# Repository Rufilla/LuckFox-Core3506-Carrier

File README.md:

<!-- {{LOGO — add the Rufilla logo here once an asset lives in this repo, e.g. }} -->

# Foxbridge — Luckfox Core3506 carrier board

<!-- Add build and release badges when CI is set up. -->

A carrier board for the [Luckfox Core3506](https://wiki.luckfox.com/Core3506/Introduction/)
system-on-module (SoM), for anyone who wants the RK3506 on a Raspberry Pi Model B-sized board
(85 × 56 mm) with Ethernet, USB-C, a DSI display & a 40-pin header. Designed in KiCad 10 by
Rufilla Ltd., from the [Luckfox Lyra Pi](https://www.luckfox.com/Luckfox-Lyra-Pi) reference
design. Revision A is a prototype: it has been built & brought up, with three hardware faults.

| | |
|---|---|
| **Client** | Internal |
| **Project code** | Foxbridge |
| **Status** | Prototype — Revision A built & reworked; Revision B in design |

> **Revision A has been built & brought up with three hardware faults.** USB host (OTG1) does
> not work without two reworks. Read the [errata](docs/errata.md) before ordering boards.

## Overview

The board breaks the Core3506 SoM out to a Raspberry Pi Model B footprint. Each subsystem has
its own schematic sheet; [docs/design-notes.md](docs/design-notes.md) explains how each one
works & why.

- **USB-C ×2** — OTG0 (device, flashing & 5 V power input) & OTG1 (host, 500 mA current limit)
- **10/100 Ethernet** — CH182H2 PHY on RMII0, HR911105A RJ45 with integrated magnetics
- **MIPI DSI** — 2-lane, 22-pin 0.5 mm FPC for the Luckfox 7" DSI touchscreen (SKU 25265)
- **40-pin header** — Raspberry Pi-compatible pinout
- **microSD** — TF-110 socket with power switching; see errata E4 for the eMMC SoM
- **RESET & RECOVERY buttons**; UART0 header & Qwiic connector (both not fitted)
- **4-layer, 1.6 mm, impedance-controlled** — built for JLCPCB Economic PCBA

Out of scope for this design:

- No on-board 3.3 V regulator is fitted; the SoM supplies `VCC_3V3`. U2 is reserved for a
  future Wi-Fi/Bluetooth module.
- No Wi-Fi or Bluetooth.
- Power comes only from 5 V on the OTG0 USB-C port — no barrel jack & no PoE.
- The microSD slot does not work with the Core3506 variant that has on-module eMMC.
- No MASKROM button & no mounting holes in Revision A.

## Requirements

**Hardware**

- Luckfox Core3506 SoM (RK3506), fitted to a Foxbridge carrier board, revision A
- USB-C cable on OTG0 for power & flashing; 3.3 V USB-UART on the UART0 header for a console
- Optional: Luckfox 7" DSI touchscreen (SKU 25265), microSD card, Ethernet cable

**Software**

- KiCad 10.0 or later. Checked with 10.0.6.
- [Fabrication Toolkit](https://github.com/bennymeg/JLC-Plugin-for-KiCad) plugin, to regenerate
  the JLCPCB production files
- Third-party symbol & footprint libraries, needed only to update a part from its library:

| Nickname in the design | Library | Install from |
|---|---|---|
| `PCM_SparkFun-*` | SparkFun KiCad Libraries | Plugin & Content Manager (PCM) |
| `PCM_*_AKL` | [Alternate KiCad Library](https://github.com/DawidCislo/Alternate-KiCad-Library) | PCM |
| `PCM_JLCPCB*` | [JLCPCB KiCad Library](https://github.com/CDFER/JLCPCB-Kicad-Library) | PCM, after adding CD_FER's repository |
| `digikey-footprints`, `dk_*` | [Digi-Key KiCad Library](https://github.com/Digi-Key/digikey-kicad-library) | Clone & register by hand (J3 only) |

PCM libraries resolve only with the default nickname prefix `PCM_` (**Preferences → Packages
& Updates**).

## Getting the source

```bash
git clone https://github.com/Rufilla/LuckFox-Core3506-Carrier.git
cd LuckFox-Core3506-Carrier
```

## Building

Open `luckfox_core3506_adapter.kicad_pro` in KiCad. The schematic & board carry a copy of every
symbol & footprint, so the design opens, plots & runs ERC/DRC without the third-party libraries
above. Parts specific to this board are in the project library `lib/` (nickname `Foxbridge`),
with their 3D models embedded.

Regenerate the fabrication outputs from the PCB editor with **Tools → External Plugins →
Fabrication Toolkit**. It reads `fabrication-toolkit-options.json`, excludes do-not-populate
parts & writes the Gerbers, drill, BOM & placement files that are committed in `production/`.

## Flashing / deployment

Ordering Revision A from JLCPCB, in full, is in
[docs/manufacturing.md](docs/manufacturing.md#order-from-jlcpcb). In short:

| File | Upload as |
|---|---|
| `production/luckfox_core3506_adapter.zip` | Gerbers & drill |
| `production/bom.csv` | Bill of materials |
| `production/positions.csv` | Component placement (CPL) |

Order Economic PCBA. Three parts are soldered by hand — J1 (RJ45), H1 (2 × 20 pin header) &
U1 (Core3506) — and the placement preview needs the rotation & offset corrections listed in the
manufacturing notes.

> **NOTE:** the files in `production/` reproduce Revision A exactly, including the faults in
> [docs/errata.md](docs/errata.md). Boards built from them need the E1 & E2 reworks before USB
> host works.

## Usage

Power the board from 5 V over the OTG0 USB-C port; the same port flashes the SoM. The console
is on the UART0 header. Ethernet, DSI & the 40-pin header need no board-level configuration.

Before trusting a freshly built board, check it against the reworks in
[docs/errata.md](docs/errata.md): R3 moved (E1) & R6/R7 bridged (E2). Photographs of both are
in `images/`.

## Testing

Run electrical rules & design rules from the project directory:

```bash
kicad-cli sch erc luckfox_core3506_adapter.kicad_sch
kicad-cli pcb drc --schematic-parity luckfox_core3506_adapter.kicad_pcb
```

Every outstanding ERC & DRC report is listed, with its cause & whether it is a real fault, in
[docs/manufacturing.md](docs/manufacturing.md#erc--drc-status). Schematic parity & unconnected
items are both zero.

## Project structure

```
luckfox_core3506_adapter.kicad_pro   KiCad project; the root schematic, 10 sheets & board sit beside it
lib/                                 Project symbol library & footprint library
production/                          Revision A files as ordered from JLCPCB: Gerbers & drill (.zip), BOM, placement, IPC netlist
docs/                                Design notes, errata, manufacturing notes & the Revision B checklist
images/                              Board render & rework photographs
```

Documentation:

- [Design notes](docs/design-notes.md) — how each subsystem works & why
- [Errata](docs/errata.md) — Revision A faults, reworks & limitations
- [Manufacturing](docs/manufacturing.md) — stack-up, ordering from JLCPCB, ERC/DRC status
- [Revision B checklist](docs/rev-b-checklist.md) — changes planned for the respin

## Security

Report a security problem to [hello@rufilla.com](mailto:hello@rufilla.com) rather than through
a public issue. This repository holds hardware design files only, so no software bill of
materials (SBOM) is produced; the bill of materials for the board is `production/bom.csv`.

## Contributing

Report problems & suggestions through GitHub issues, & send changes as pull requests.

## Licence

Copyright 2026 Rufilla Ltd. Licensed under the [Apache License 2.0](LICENSE).

Symbols, footprints & 3D models copied from third-party libraries remain under their own
licences.

## Support

Rufilla Ltd · Building D5, Culham Campus, Abingdon, Oxfordshire, UK, OX14 3DB
[hello@rufilla.com](mailto:hello@rufilla.com) · +44 (0)1865 601201 · [www.rufilla.com](https://www.rufilla.com)

© 2026 Rufilla Ltd

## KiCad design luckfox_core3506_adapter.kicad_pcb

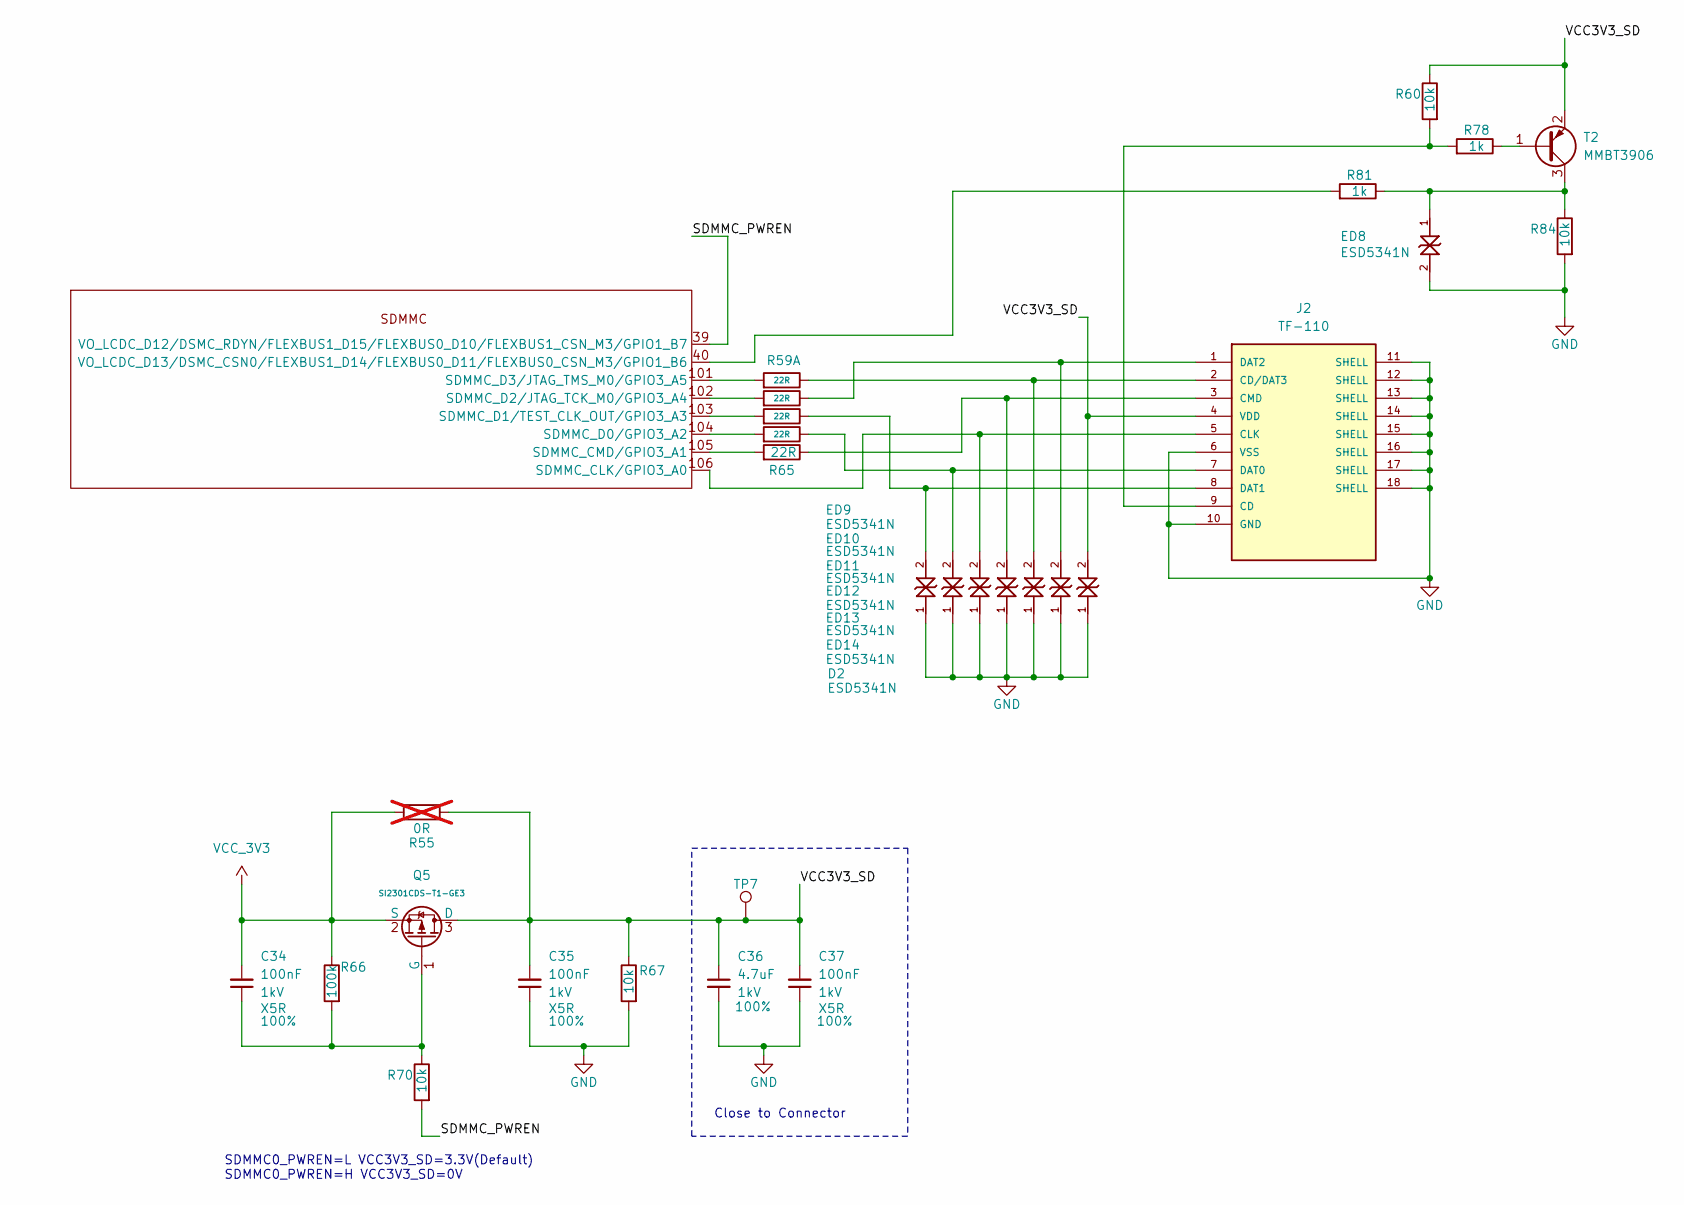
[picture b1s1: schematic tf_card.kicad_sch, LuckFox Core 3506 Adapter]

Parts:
C34, C35, C37: 100nF; C_0603_1608Metric; Voltage 1kV; Tolerance 100%; LCSC C14663
C36: 4.7uF; C_0603_1608Metric; Voltage 1kV; Tolerance 100%; LCSC C19666
D2: ESD5341N; D_0402_1005Metric; LCSC C20612964
ED8, ED9, ED10, ED11, ED12, ED13, ED14: ESD5341N; D_0402_1005Metric; LCSC C20612964
J2: TF-110; TF-SMD_TF-110; LCSC C266613
Q5: SI2301CDS-T1-GE3; Q_SOT-23; Part SI2301CDS-T1-GE3; LCSC C10487
R55: 0R; R_0603_1608Metric; LCSC C21189; not fitted
R59: 22R; R_0603x4; Tolerance ±5%; Part 4D03WGJ0220T5E; LCSC C12008
R60, R67, R70, R84: 10k; R_0603_1608Metric; LCSC C25804
R65: 22R; R_0603_1608Metric; LCSC C23345
R66: 100k; R_0603_1608Metric; LCSC C25803
R78, R81: 1k; R_0603_1608Metric; LCSC C21190
T2: MMBT3906; SOT23-3; LCSC C2149
TP7: 3.3v SD; TestPoint-1.0mm
U1: CORE3506_[32_32]_120P

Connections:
/TF card/SDMMC_PWREN: R70.1, U1.39 (VO_LCDC_D12/DSMC_RDYN/FLEXBUS1_D15/FLEX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)
/TF card/VCC3V3_SD: C35.2, C36.1, C37.2, D2.2 (A2), J2.4 (VDD), Q5.3 (D), R55.1, R60.2, R67.2, T2.2 (E), TP7.1 (1_1)
GND: C35.1, C36.2, C37.1, D2.1 (A1), ED8.2 (A2), ED9.1 (A1), ED10.1 (A1), ED11.1 (A1), ED12.1 (A1), ED13.1 (A1), ED14.1 (A1), J2.6 (VSS), J2.10 (GND), J2.11 (SHELL), J2.12 (SHELL), J2.13 (SHELL), J2.14 (SHELL), J2.15 (SHELL), J2.16 (SHELL), J2.17 (SHELL), J2.18 (SHELL), R67.1, R84.1; also elsewhere on the board
unnamed: ED8.1 (A1), R81.2, R84.2, T2.3 (C)
unnamed: ED9.2 (A2), J2.8 (DAT1), R59.7
unnamed: ED10.2 (A2), J2.7 (DAT0), R59.8
unnamed: ED11.2 (A2), J2.5 (CLK), U1.106 (SDMMC_CLK/GPIO3_A0)
unnamed: ED12.2 (A2), J2.3 (CMD), R65.2
unnamed: ED13.2 (A2), J2.2 (CD/DAT3), R59.5
unnamed: ED14.2 (A2), J2.1 (DAT2), R59.6
unnamed: J2.9 (CD), R60.1, R78.1
unnamed: C34.1, Q5.1 (G), R66.1, R70.2
unnamed: R78.2, T2.1 (B)
unnamed: R65.1, U1.105 (SDMMC_CMD/GPIO3_A1)
unnamed: R59.1, U1.104 (SDMMC_D0/GPIO3_A2)
unnamed: R59.2, U1.103 (SDMMC_D1/TEST_CLK_OUT/GPIO3_A3)
unnamed: R59.3, U1.102 (SDMMC_D2/JTAG_TCK_M0/GPIO3_A4)
unnamed: R59.4, U1.101 (SDMMC_D3/JTAG_TMS_M0/GPIO3_A5)
unnamed: R81.1, U1.40 (VO_LCDC_D13/DSMC_CSN0/FLEXBUS1_D14/FLEX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)
VCC_3V3: C34.2, Q5.2 (S), R55.2, R66.2; also elsewhere on the board

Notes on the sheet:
Close to Connector
SDMMC0_PWREN=L VCC3V3_SD=3.3V(Default) SDMMC0_PWREN=H VCC3V3_SD=0V

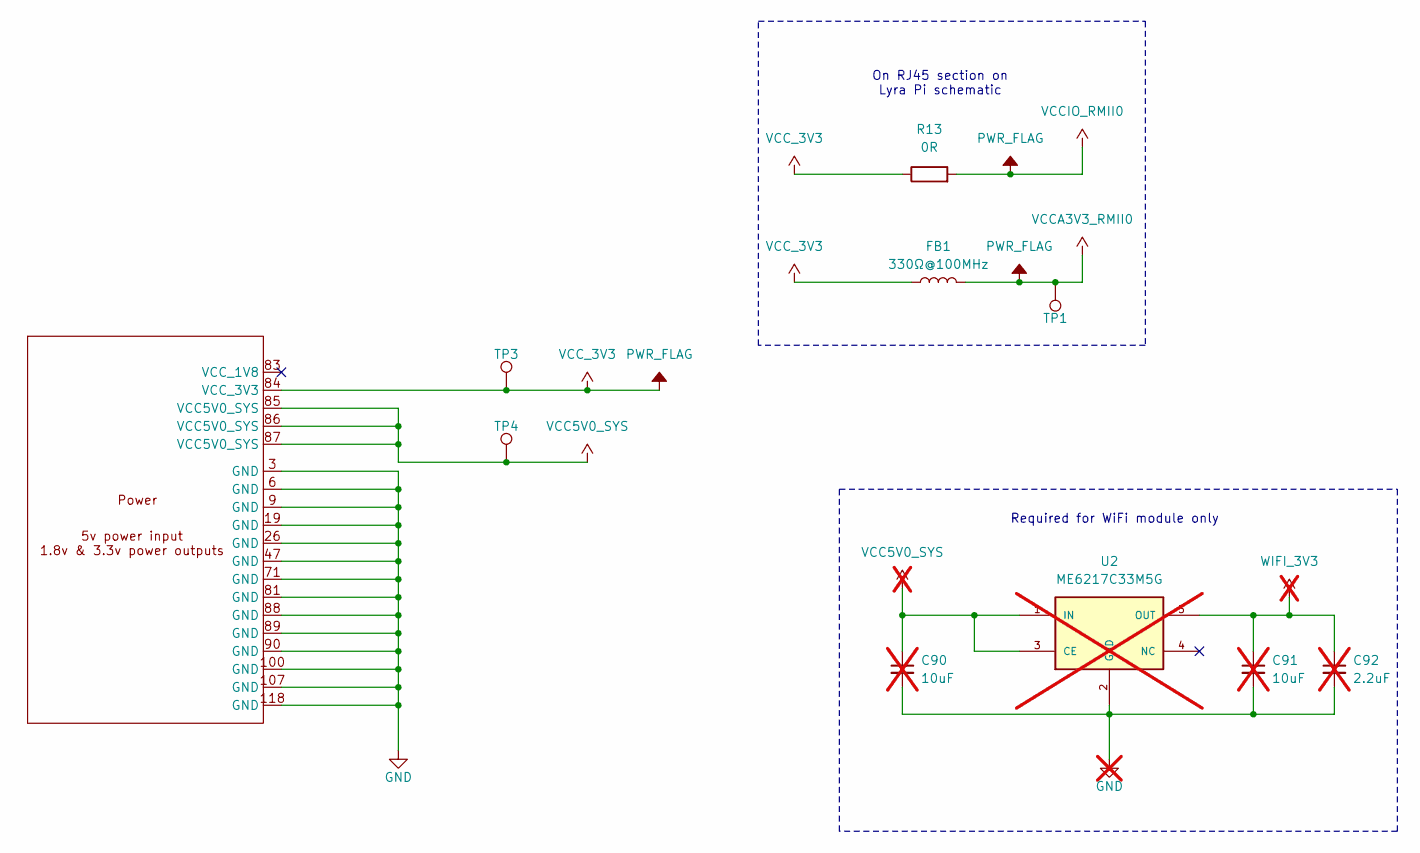
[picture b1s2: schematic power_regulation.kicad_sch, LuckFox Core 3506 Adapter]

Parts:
C90, C91: 10uF; C_0603_1608Metric; LCSC C19702; not fitted
C92: 2.2uF; C_0603_1608Metric; LCSC C23630; not fitted
FB1: 330Ω@100MHz; L_0603_1608Metric; LCSC C88989
R13: 0R; R_0603_1608Metric; LCSC C21189
TP1: 3.3v RMIIO; TestPoint-1.0mm
TP3: 3.3v; TestPoint-1.0mm
TP4: 5v; TestPoint-1.0mm
U1: CORE3506_[32_32]_120P
U2: ME6217C33M5G; SOT23-5; M_PART_NUMBER ME6217C33M5G; LCSC C427602; not fitted

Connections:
GND: C90.2, C91.2, C92.2, U1.3 (GND), U1.6 (GND), U1.9 (GND), U1.19 (GND), U1.26 (GND), U1.47 (GND), U1.71 (GND), U1.81 (GND), U1.88 (GND), U1.89 (GND), U1.90 (GND), U1.100 (GND), U1.107 (GND), U1.118 (GND), U2.2 (GND); also elsewhere on the board
VCC5V0_SYS: C90.1, TP4.1 (1_1), U1.85 (VCC5V0_SYS), U1.86 (VCC5V0_SYS), U1.87 (VCC5V0_SYS), U2.1 (IN), U2.3 (CE); also elsewhere on the board
VCCA3V3_RMII0: FB1.2, TP1.1 (1_1); also elsewhere on the board
VCCIO_RMII0: R13.2; also elsewhere on the board
VCC_3V3: FB1.1, R13.1, TP3.1 (1_1), U1.84 (VCC_3V3); also elsewhere on the board
WIFI_3V3: C91.1, C92.1, U2.5 (OUT)

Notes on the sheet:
On RJ45 section on Lyra Pi schematic
Required for WiFi module only

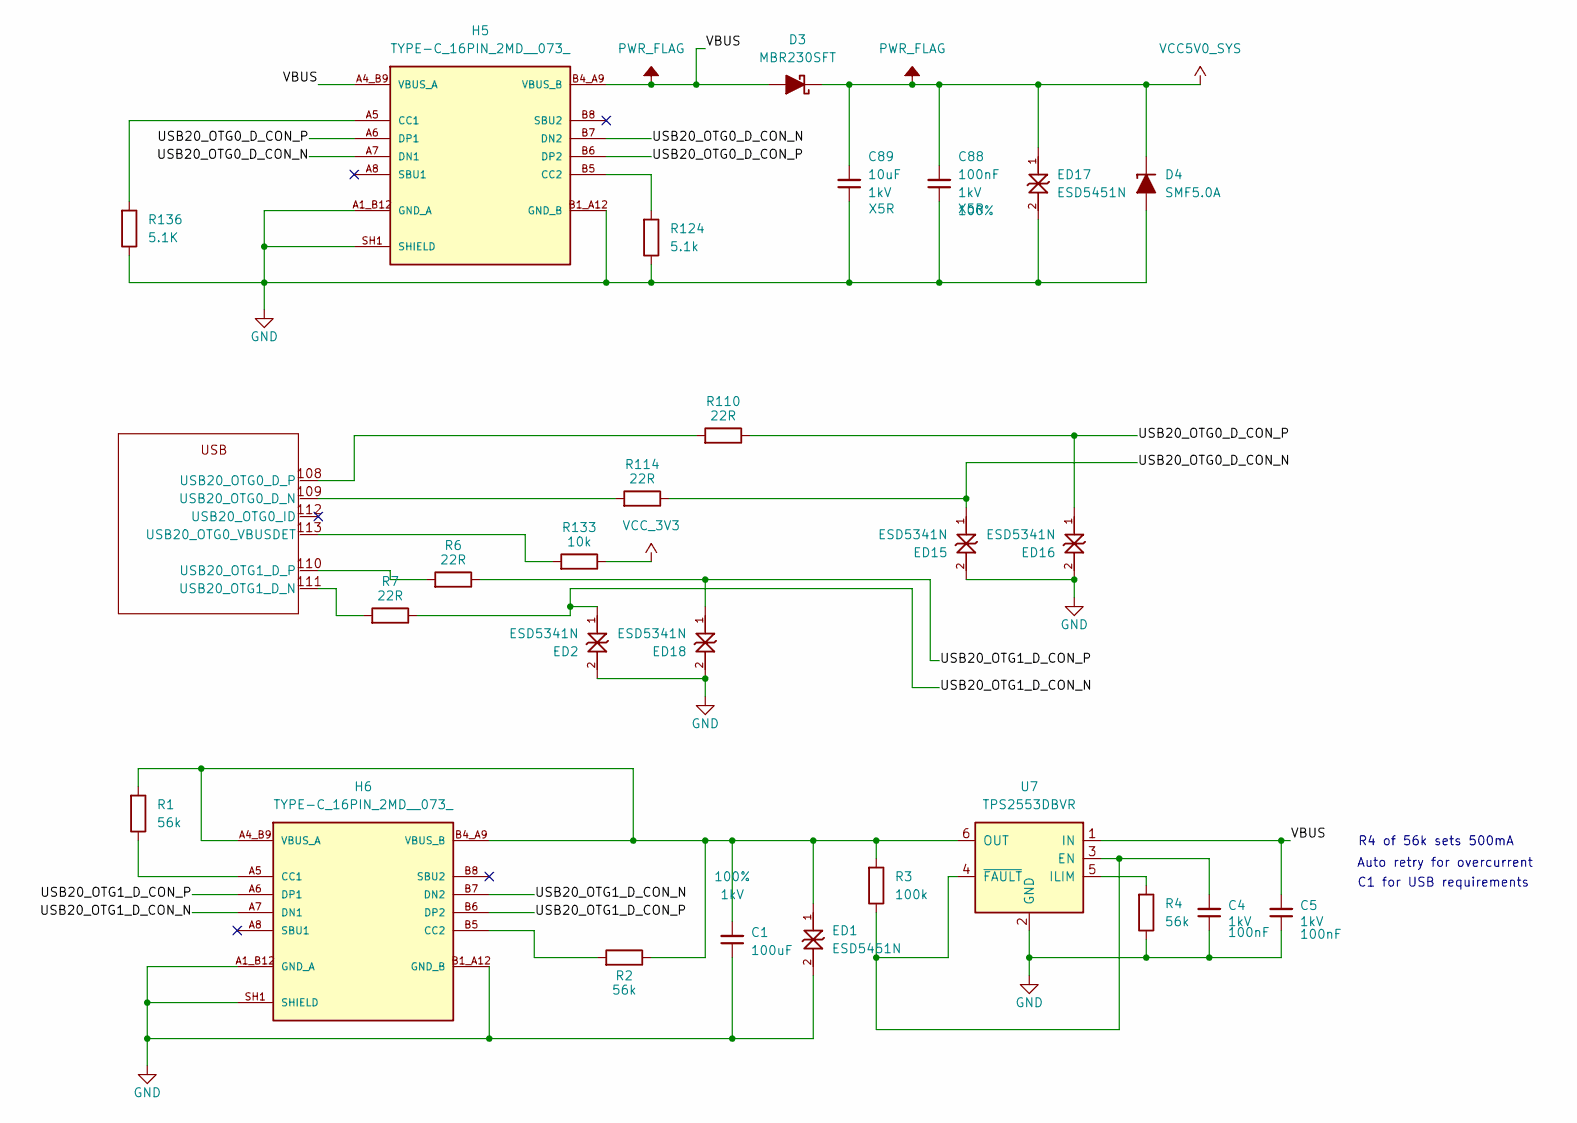
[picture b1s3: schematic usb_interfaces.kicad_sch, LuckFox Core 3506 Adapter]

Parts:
C1: 100uF; C_1206_3216Metric; Voltage 1kV; Tolerance 100%; LCSC C15008
C4, C5, C88: 100nF; C_0603_1608Metric; Voltage 1kV; Tolerance 100%; LCSC C14663
C89: 10uF; C_0603_1608Metric; Voltage 1kV; Tolerance 100%; LCSC C19702
D3: MBR230SFT; D_SOD-123F; LCSC C5377812
D4: SMF5.0A; D_SOD-123F; LCSC C19077498
ED1, ED17: ESD5451N; D_0402_1005Metric; LCSC C2936977
ED2, ED15, ED16, ED18: ESD5341N; D_0402_1005Metric; LCSC C20612964
H5, H6: TYPE-C_16PIN_2MD__073_; TYPE-C_16PIN_2MD_073; LCSC C2765186
R1, R2, R4: 56k; R_0603_1608Metric; LCSC C23206
R3: 100k; R_0603_1608Metric; LCSC C25803
R6, R7, R110, R114: 22R; R_0603_1608Metric; LCSC C23345
R124: 5.1k; R_0603_1608Metric; LCSC C23186
R133: 10k; R_0603_1608Metric; LCSC C25804
R136: 5.1K; R_0603_1608Metric; LCSC C23186
U1: CORE3506_[32_32]_120P
U7: TPS2553DBVR; SOT-23-6; LCSC C55266

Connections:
/USB interfaces/USB20_OTG0_D_CON_N: ED15.1 (A1), H5.A7 (DN1), H5.B7 (DN2), R114.2
/USB interfaces/USB20_OTG0_D_CON_P: ED16.1 (A1), H5.A6 (DP1), H5.B6 (DP2), R110.2
/USB interfaces/USB20_OTG1_D_CON_N: ED2.1 (A1), H6.A7 (DN1), H6.B7 (DN2), R7.2
/USB interfaces/USB20_OTG1_D_CON_P: ED18.1 (A1), H6.A6 (DP1), H6.B6 (DP2), R6.2
/USB interfaces/VBUS: C5.2, D3.2 (A), H5.A4_B9 (VBUS_A), H5.B4_A9 (VBUS_B), U7.1 (IN)
GND: C1.1, C4.1, C5.1, C88.1, C89.1, D4.2 (A), ED1.2 (A2), ED2.2 (A2), ED15.2 (A2), ED16.2 (A2), ED17.2 (A2), ED18.2 (A2), H5.A1_B12 (GND_A), H5.B1_A12 (GND_B), H5.SH1 (SHIELD), H5.SH2 (SHIELD), H5.SH3 (SHIELD), H5.SH4 (SHIELD), H6.A1_B12 (GND_A), H6.B1_A12 (GND_B), H6.SH1 (SHIELD), H6.SH2 (SHIELD), H6.SH3 (SHIELD), H6.SH4 (SHIELD), R4.2, R124.2, R136.2, U7.2 (GND); also elsewhere on the board
unnamed: C1.2, ED1.1 (A1), H6.A4_B9 (VBUS_A), H6.B4_A9 (VBUS_B), R1.1, R2.2, R3.1, U7.6 (OUT)
unnamed: H5.A5 (CC1), R136.1
unnamed: H5.B5 (CC2), R124.1
unnamed: H6.A5 (CC1), R1.2
unnamed: H6.B5 (CC2), R2.1
unnamed: R114.1, U1.109 (USB20_OTG0_D_N)
unnamed: R110.1, U1.108 (USB20_OTG0_D_P)
unnamed: R133.1, U1.113 (USB20_OTG0_VBUSDET)
unnamed: R7.1, U1.111 (USB20_OTG1_D_N)
unnamed: R6.1, U1.110 (USB20_OTG1_D_P)
unnamed: C4.2, R3.2, U7.3 (EN), U7.4 (~FAULT)
unnamed: R4.1, U7.5 (ILIM)
VCC5V0_SYS: C88.2, C89.2, D3.1 (K), D4.1 (K), ED17.1 (A1); also elsewhere on the board
VCC_3V3: R133.2; also elsewhere on the board

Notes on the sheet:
R4 of 56k sets 500mA
C1 for USB requirements
Auto retry for overcurrent

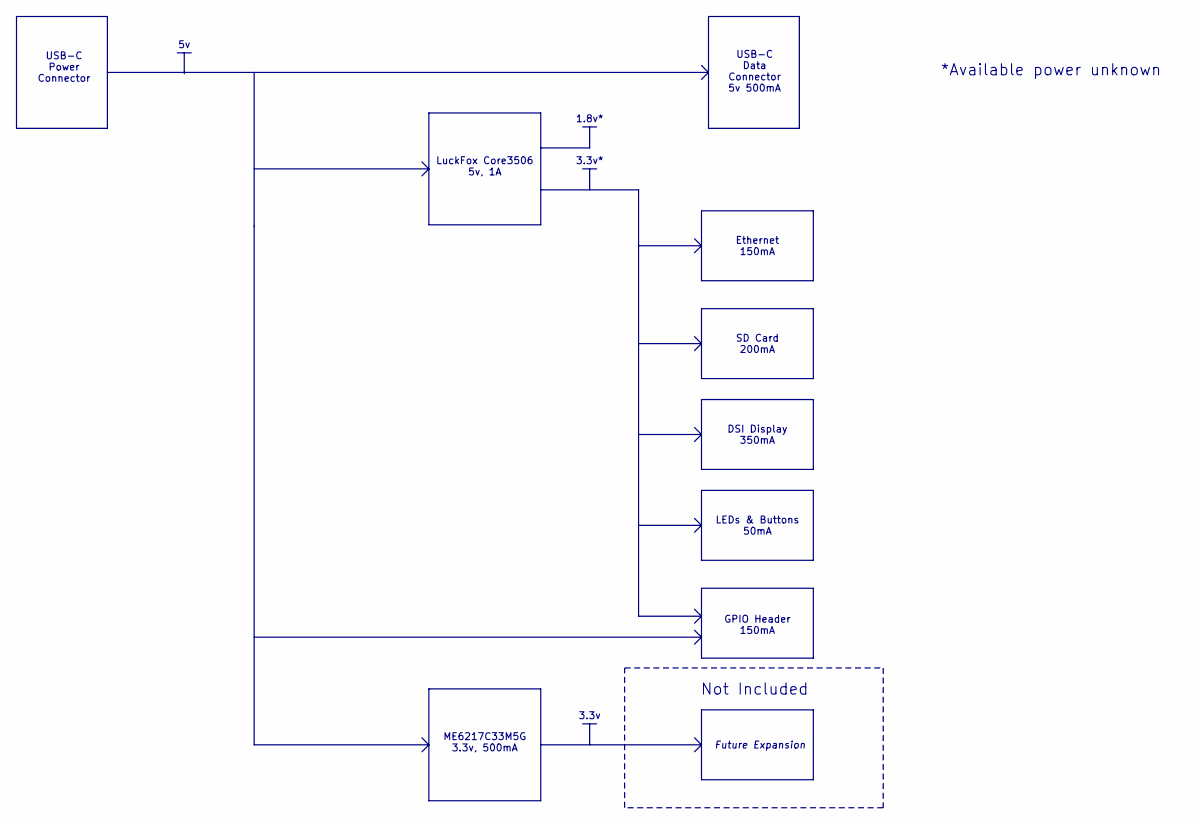
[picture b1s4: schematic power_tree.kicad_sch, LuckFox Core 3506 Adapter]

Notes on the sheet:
GPIO Header 150mA
Ethernet 150mA
*Available power unknown
DSI Display 350mA
LEDs & Buttons 50mA
USB-C Data Connector 5v 500mA
3.3v
USB-C Power Connector
1.8v*
LuckFox Core3506 5v, 1A
ME6217C33M5G 3.3v, 500mA
3.3v*
SD Card 200mA
Not Included
Future Expansion

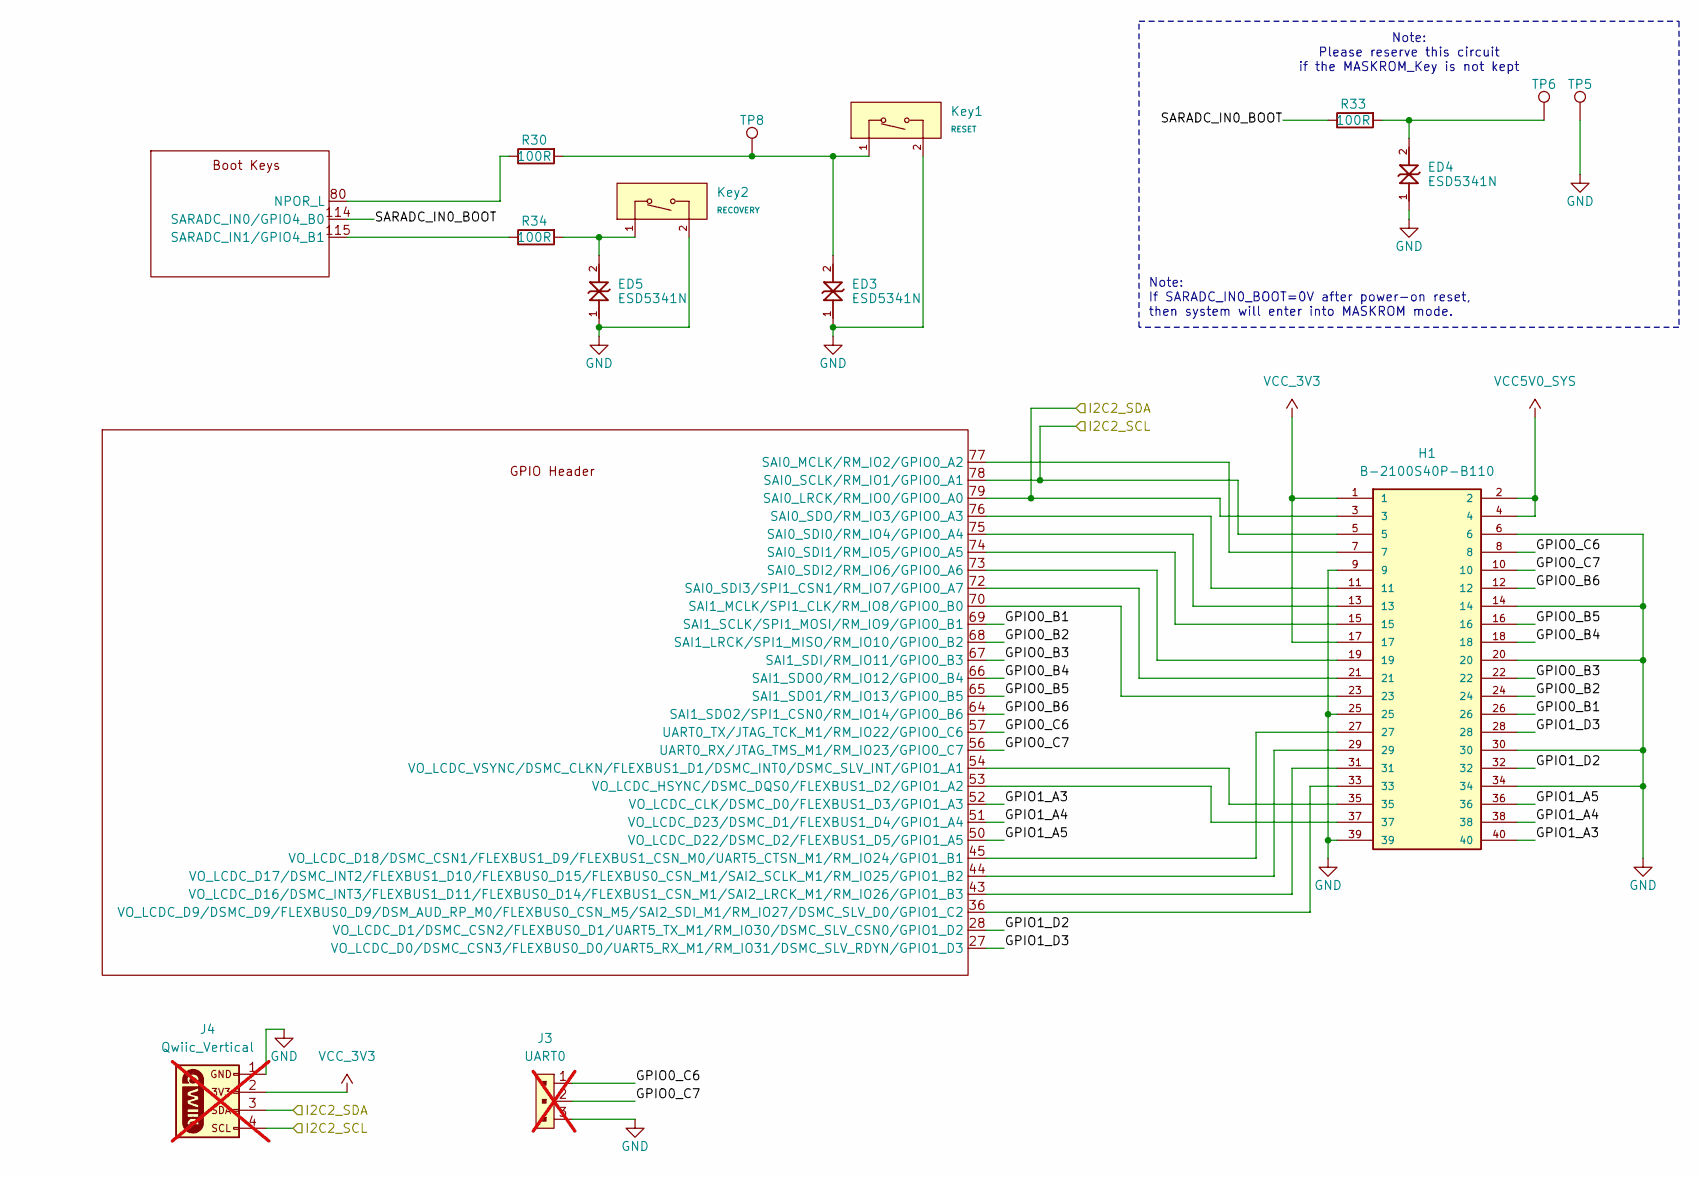
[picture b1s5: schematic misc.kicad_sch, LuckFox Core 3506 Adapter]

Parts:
ED3, ED4, ED5: ESD5341N; D_0402_1005Metric; LCSC C20612964
H1: B-2100S40P-B110; PinHeader_2x20_P2.54mm_Vertical; LCSC C124383
J3: UART0; PinHeader_1x3_P2.54_Drill1.1mm; MPN 640456-3; Digi-Key_PN A19470-ND; not fitted
J4: Qwiic_Vertical; JST_1x04_P1.0mm_Vertical_SMD; not fitted
Key1: RESET; SW_TS-1088-AR02016; Voltage Rating (Dc) 12V; Part TS-1088-AR02016; LCSC C720477
Key2: RECOVERY; SW_TS-1088-AR02016; Voltage Rating (Dc) 12V; Part TS-1088-AR02016; LCSC C720477
R30, R33, R34: 100R; R_0603_1608Metric; LCSC C22775
TP5: GND; TestPoint-1.0mm
TP6: BOOT; TestPoint-1.0mm
TP8: NPOR_L; TestPoint-1.0mm
U1: CORE3506_[32_32]_120P

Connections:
/DSI/I2C2_SCL: H1.5, J4.4, U1.78 (SAI0_SCLK/RM_IO1/GPIO0_A1); also elsewhere on the board
/DSI/I2C2_SDA: H1.3, J4.3, U1.79 (SAI0_LRCK/RM_IO0/GPIO0_A0); also elsewhere on the board
/GPIO Header & boot keys/GPIO0_B1: H1.26, U1.69 (SAI1_SCLK/SPI1_MOSI/RM_IO9/GPIO0_B1)
/GPIO Header & boot keys/GPIO0_B2: H1.24, U1.68 (SAI1_LRCK/SPI1_MISO/RM_IO10/GPIO0_B2)
/GPIO Header & boot keys/GPIO0_B3: H1.22, U1.67 (SAI1_SDI/RM_IO11/GPIO0_B3)
/GPIO Header & boot keys/GPIO0_B4: H1.18, U1.66 (SAI1_SDO0/RM_IO12/GPIO0_B4)
/GPIO Header & boot keys/GPIO0_B5: H1.16, U1.65 (SAI1_SDO1/RM_IO13/GPIO0_B5)
/GPIO Header & boot keys/GPIO0_B6: H1.12, U1.64 (SAI1_SDO2/SPI1_CSN0/RM_IO14/GPIO0_B6)
/GPIO Header & boot keys/GPIO0_C6: H1.8, J3.1, U1.57 (UART0_TX/JTAG_TCK_M1/RM_IO22/GPIO0_C6)
/GPIO Header & boot keys/GPIO0_C7: H1.10, J3.2, U1.56 (UART0_RX/JTAG_TMS_M1/RM_IO23/GPIO0_C7)
/GPIO Header & boot keys/GPIO1_A3: H1.40, U1.52 (VO_LCDC_CLK/DSMC_D0/FLEXBUS1_D3/GPIO1_A3)
/GPIO Header & boot keys/GPIO1_A4: H1.38, U1.51 (VO_LCDC_D23/DSMC_D1/FLEXBUS1_D4/GPIO1_A4)
/GPIO Header & boot keys/GPIO1_A5: H1.36, U1.50 (VO_LCDC_D22/DSMC_D2/FLEXBUS1_D5/GPIO1_A5)
/GPIO Header & boot keys/GPIO1_D2: H1.32, U1.28 (VO_LCDC_D1/DSMC_CSN2/FLEXBUS0_D1/UART5_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)
/GPIO Header & boot keys/GPIO1_D3: H1.28, U1.27 (VO_LCDC_D0/DSMC_CSN3/FLEXBUS0_D0/UART5_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)
/GPIO Header & boot keys/SARADC_IN0_BOOT: R33.2, U1.114 (SARADC_IN0/GPIO4_B0)
GND: ED3.1 (A1), ED4.1 (A1), ED5.1 (A1), H1.6, H1.9, H1.14, H1.20, H1.25, H1.30, H1.34, H1.39, J3.3, J4.1, Key1.2 (B), Key2.2 (B), TP5.1 (1_1); also elsewhere on the board
unnamed: ED3.2 (A2), Key1.1 (A), R30.1, TP8.1 (1_1)
unnamed: ED4.2 (A2), R33.1, TP6.1 (1_1)
unnamed: ED5.2 (A2), Key2.1 (A), R34.1
unnamed: R30.2, U1.80 (NPOR_L)
unnamed: R34.2, U1.115 (SARADC_IN1/GPIO4_B1)
unnamed: H1.7, U1.77 (SAI0_MCLK/RM_IO2/GPIO0_A2)
unnamed: H1.13, U1.75 (SAI0_SDI0/RM_IO4/GPIO0_A4)
unnamed: H1.15, U1.74 (SAI0_SDI1/RM_IO5/GPIO0_A5)
unnamed: H1.19, U1.73 (SAI0_SDI2/RM_IO6/GPIO0_A6)
unnamed: H1.21, U1.72 (SAI0_SDI3/SPI1_CSN1/RM_IO7/GPIO0_A7)
unnamed: H1.11, U1.76 (SAI0_SDO/RM_IO3/GPIO0_A3)
unnamed: H1.23, U1.70 (SAI1_MCLK/SPI1_CLK/RM_IO8/GPIO0_B0)
unnamed: H1.33, U1.36 (VO_LCDC_D9/DSMC_D9/FLEXBUS0_D9/DSM_AUD_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)
unnamed: H1.31, U1.43 (VO_LCDC_D16/DSMC_INT3/FLEXBUS1_D11/FLEX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)
unnamed: H1.29, U1.44 (VO_LCDC_D17/DSMC_INT2/FLEXBUS1_D10/FLEX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)
unnamed: H1.27, U1.45 (VO_LCDC_D18/DSMC_CSN1/FLEXBUS1_D9/FLEXB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)
unnamed: H1.37, U1.53 (VO_LCDC_HSYNC/DSMC_DQS0/FLEXBUS1_D2/GPI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)
unnamed: H1.35, U1.54 (VO_LCDC_VSYNC/DSMC_CLKN/FLEXBUS1_D1/DSM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)
VCC5V0_SYS: H1.2, H1.4; also elsewhere on the board
VCC_3V3: H1.1, H1.17, J4.2; also elsewhere on the board

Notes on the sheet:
Note: Please reserve this circuit if the MASKROM_Key is not kept
Note: If SARADC_IN0_BOOT=0V after power-on reset, then system will enter into MASKROM mode.

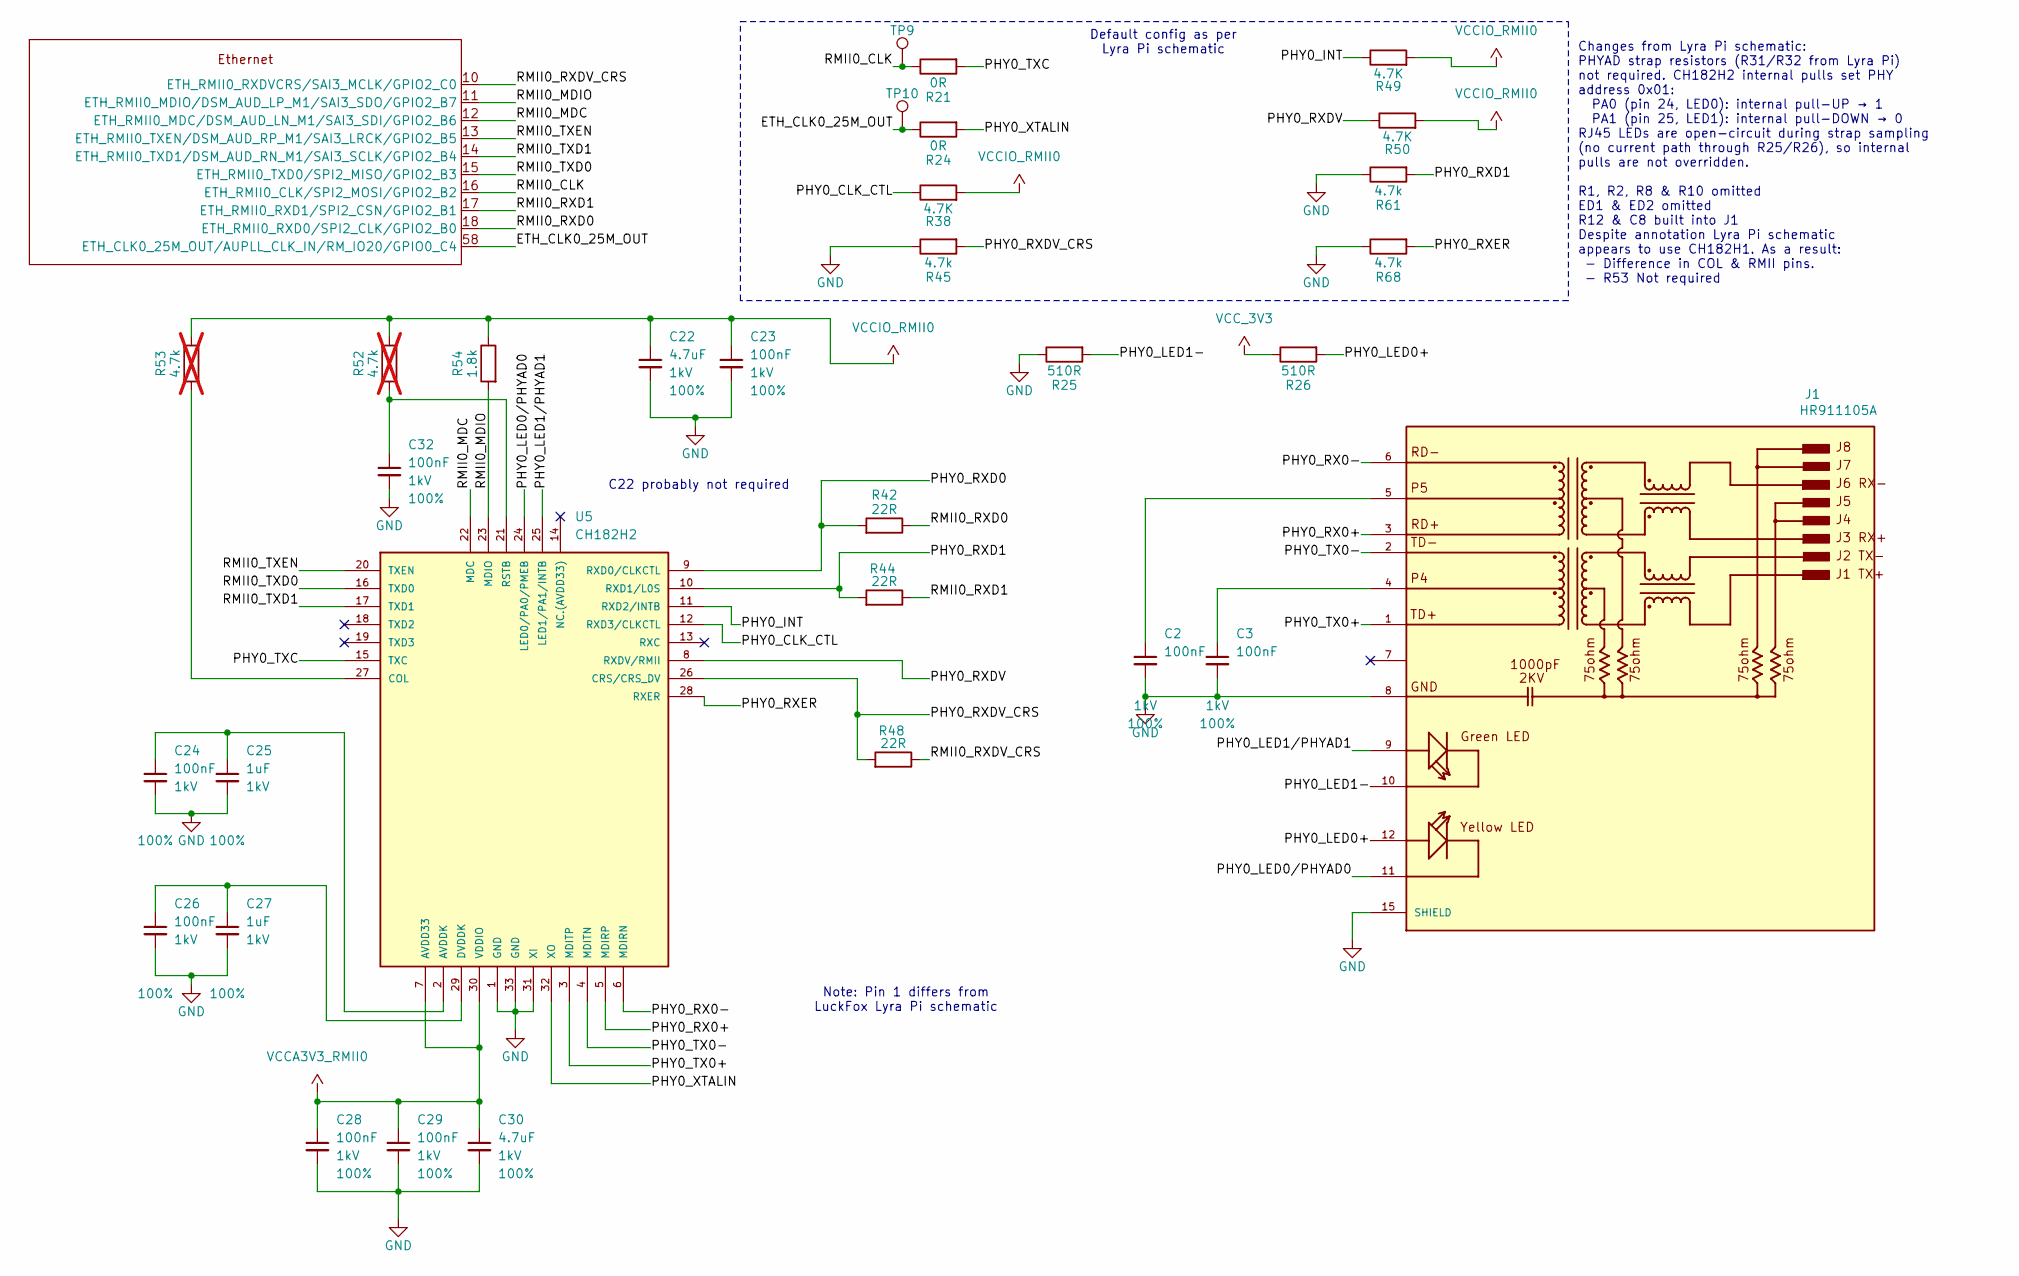
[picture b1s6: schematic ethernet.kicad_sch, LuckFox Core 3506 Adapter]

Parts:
C2, C3, C23, C24, C26, C28, C29, C32: 100nF; C_0603_1608Metric; Voltage 1kV; Tolerance 100%; LCSC C14663
C22, C30: 4.7uF; C_0603_1608Metric; Voltage 1kV; Tolerance 100%; LCSC C19666
C25, C27: 1uF; C_0603_1608Metric; Voltage 1kV; Tolerance 100%; LCSC C15849
J1: HR911105A; HANRUN_HR911105A; LCSC C12074
R21, R24: 0R; R_0603_1608Metric; LCSC C21189
R25, R26: 510R; R_0603_1608Metric; LCSC C23193
R38, R49, R50: 4.7K; R_0603_1608Metric; LCSC C23162
R42, R44, R48: 22R; R_0603_1608Metric; LCSC C23345
R45, R61, R68: 4.7k; R_0603_1608Metric; LCSC C23162
R52, R53: 4.7k; R_0603_1608Metric; LCSC C23162; not fitted
R54: 1.8k; R_0603_1608Metric; LCSC C4177
TP9: RMII0_CLK; TestPoint-1.0mm
TP10: ETH_CLK; TestPoint-1.0mm
U1: CORE3506_[32_32]_120P
U5: CH182H2; QFN-32-1EP_5x5mm_P0.5mm_EP3.45x3.45mm; LCSC C41427683

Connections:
/Ethernet/ETH_CLK0_25M_OUT: R24.2, TP10.1 (1_1), U1.58 (ETH_CLK0_25M_OUT/AUPLL_CLK_IN/RM_IO20/G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)
/Ethernet/PHY0_CLK_CTL: R38.1, U5.12 (RXD3/CLKCTL)
/Ethernet/PHY0_INT: R49.1, U5.11 (RXD2/INTB)
/Ethernet/PHY0_LED0+: J1.12, R26.1
/Ethernet/PHY0_LED0/PHYAD0: J1.11, U5.24 (LED0/PA0/PMEB)
/Ethernet/PHY0_LED1-: J1.10, R25.1
/Ethernet/PHY0_LED1/PHYAD1: J1.9, U5.25 (LED1/PA1/INTB)
/Ethernet/PHY0_RX0+: J1.3, U5.5 (MDIRP)
/Ethernet/PHY0_RX0-: J1.6, U5.6 (MDIRN)
/Ethernet/PHY0_RXD0: R42.1, U5.9 (RXD0/CLKCTL)
/Ethernet/PHY0_RXD1: R44.1, R61.1, U5.10 (RXD1/L0S)
/Ethernet/PHY0_RXDV: R50.1, U5.8 (RXDV/RMII)
/Ethernet/PHY0_RXDV_CRS: R45.1, R48.1, U5.26 (CRS/CRS_DV)
/Ethernet/PHY0_RXER: R68.1, U5.28 (RXER)
/Ethernet/PHY0_TX0+: J1.1, U5.3 (MDITP)
/Ethernet/PHY0_TX0-: J1.2, U5.4 (MDITN)
/Ethernet/PHY0_TXC: R21.1, U5.15 (TXC)
/Ethernet/PHY0_XTALIN: R24.1, U5.32 (XO)
/Ethernet/RMII0_CLK: R21.2, TP9.1 (1_1), U1.16 (ETH_RMII0_CLK/SPI2_MOSI/GPIO2_B2)
/Ethernet/RMII0_MDC: U1.12 (ETH_RMII0_MDC/DSM_AUD_LN_M1/SAI3_SDI/GP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), U5.22 (MDC)
/Ethernet/RMII0_MDIO: R54.1, U1.11 (ETH_RMII0_MDIO/DSM_AUD_LP_M1/SAI3_SDO/G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), U5.23 (MDIO)
/Ethernet/RMII0_RXD0: R42.2, U1.18 (ETH_RMII0_RXD0/SPI2_CLK/GPIO2_B0)
/Ethernet/RMII0_RXD1: R44.2, U1.17 (ETH_RMII0_RXD1/SPI2_CSN/GPIO2_B1)
/Ethernet/RMII0_RXDV_CRS: R48.2, U1.10 (ETH_RMII0_RXDVCRS/SAI3_MCLK/GPIO2_C0)
/Ethernet/RMII0_TXD0: U1.15 (ETH_RMII0_TXD0/SPI2_MISO/GPIO2_B3), U5.16 (TXD0)
/Ethernet/RMII0_TXD1: U1.14 (ETH_RMII0_TXD1/DSM_AUD_RN_M1/SAI3_SCLK/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), U5.17 (TXD1)
/Ethernet/RMII0_TXEN: U1.13 (ETH_RMII0_TXEN/DSM_AUD_RP_M1/SAI3_LRCK/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), U5.20 (TXEN)
GND: C2.2, C3.2, C22.2, C23.2, C24.2, C25.2, C26.2, C27.2, C28.2, C29.2, C30.2, C32.2, J1.8, J1.15 (SHIELD), J1.16 (SHIELD), R25.2, R45.2, R61.2, R68.2, U5.1 (GND), U5.31 (XI), U5.33 (GND); also elsewhere on the board
unnamed: C2.1, J1.5
unnamed: C3.1, J1.4
unnamed: C24.1, C25.1, U5.2 (AVDDK)
unnamed: R53.1, U5.27 (COL)
unnamed: C26.1, C27.1, U5.29 (DVDDK)
unnamed: C32.1, R52.1, U5.21 (RSTB)
VCCA3V3_RMII0: C28.1, C29.1, C30.1, U5.7 (AVDD33), U5.30 (VDDIO); also elsewhere on the board
VCCIO_RMII0: C22.1, C23.1, R38.2, R49.2, R50.2, R52.2, R53.2, R54.2; also elsewhere on the board
VCC_3V3: R26.2; also elsewhere on the board

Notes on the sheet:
Default config as per Lyra Pi schematic
Note: Pin 1 differs from LuckFox Lyra Pi schematic
C22 probably not required
Changes from Lyra Pi schematic: PHYAD strap resistors (R31/R32 from Lyra Pi) not required. CH182H2 internal pulls set PHY address 0x01: PA0 (pin 24, LED0): internal pull-UP → 1 PA1 (pin 25, LED1): internal pull-DOWN → 0 RJ45 LEDs are open-circuit during strap sampling (no current path through R25/R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

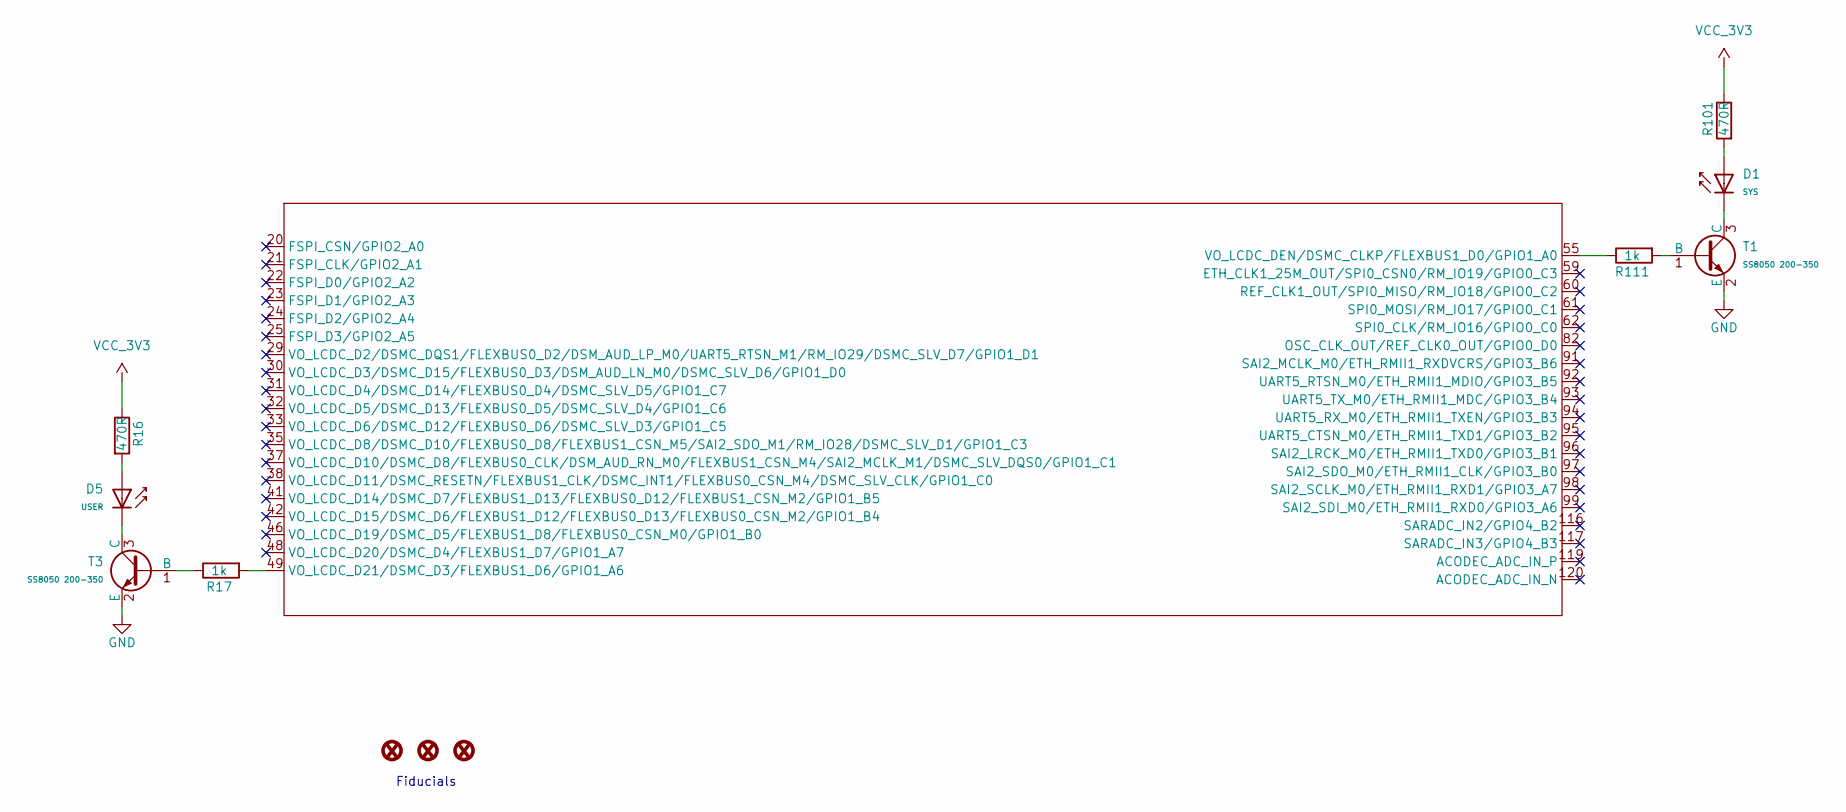
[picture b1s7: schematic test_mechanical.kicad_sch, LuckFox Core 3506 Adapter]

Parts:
D1: SYS; D_0805; Part KT-0805G; LCSC C2297
D5: USER; D_0805; Part KT-0805G; LCSC C2297
FID1, FID2, FID3: Fiducial_0.5mm; Fiducial_1mm_Mask2mm
R16, R101: 470R; R_0603_1608Metric; LCSC C23179
R17, R111: 1k; R_0603_1608Metric; LCSC C21190
T1, T3: SS8050 200-350; Q_SOT-23; Part SS8050(RANGE:200-350); LCSC C2150
U1: CORE3506_[32_32]_120P

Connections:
GND: T1.2 (E), T3.2 (E); also elsewhere on the board
unnamed: D1.2, R101.1
unnamed: D5.2, R16.1
unnamed: R111.1, T1.1 (B)
unnamed: D1.1, T1.3 (C)
unnamed: R17.2, T3.1 (B)
unnamed: D5.1, T3.3 (C)
unnamed: R17.1, U1.49 (VO_LCDC_D21/DSMC_D3/FLEXBUS1_D6/GPIO1_A6)
unnamed: R111.2, U1.55 (VO_LCDC_DEN/DSMC_CLKP/FLEXBUS1_D0/GPIO1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)
VCC_3V3: R16.2, R101.2; also elsewhere on the board

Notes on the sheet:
Fiducials

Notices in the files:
README.md:
Licence: Apache 2.0
block.kicad_sch:
SPDX-License-Identifier: Apache-2.0
